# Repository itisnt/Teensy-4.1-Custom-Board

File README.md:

# Teensy-4.1-Custom-Board

Simple Board for a Teensy 4.1 with Ethernet, 2 x I2C, RX1/TX1/GND and the power pins on sockets or pins. I created the board to use it as a sensor board with a Sensirion SHT35D Temp/Humy sensor and a Adafruit four 7-segmented LED Display board.  But maybe somebody can use it for different purposes. 

You need (beside the PCB...):
- A Teensy 4.1 board https://www.pjrc.com/store/teensy41.html
- The Ethernet kit https://www.pjrc.com/store/ethernet_kit.html (you need the MagJack, the capacitor and maybe the headers)
- Additional sockets and headers to make the Teensy removable. 
- If you use I2C, you should add the two SMD 0603 resistors (1 - 10kohm). There are internal pull-ups in the Teensy, but they are quite weak

## Some remarks:
- It's my first KiCad board, so a lot of things will be wrong (i assume...)
- Since i use https://aisler.com to produce the PCB and Aisler allows to simply upload the _pcb file from KiCad, all the Gerber stuff is untested. So don't simply upload the gerber files. Setup KiCad 8 and create your own gerber files
- KiCad 8.0.4 was used
- Since i didn't find the right MagJack in KiCad i had to edit the Symbol for one of the MagJack available in KiCad. What i did was reordering R1-R8. Thats why there is a custom lib. And also you need the Teensy Lib which i've found somewhere in the internet. 
- I do not sell any PCB's

## Ideas for the future:
- Make more pins available (SPI foremost)
- Center the top I2C header so that the Adafruit 4-Segment Display is more in the middle of the board
- Maybe add an FRAM (SPI based)

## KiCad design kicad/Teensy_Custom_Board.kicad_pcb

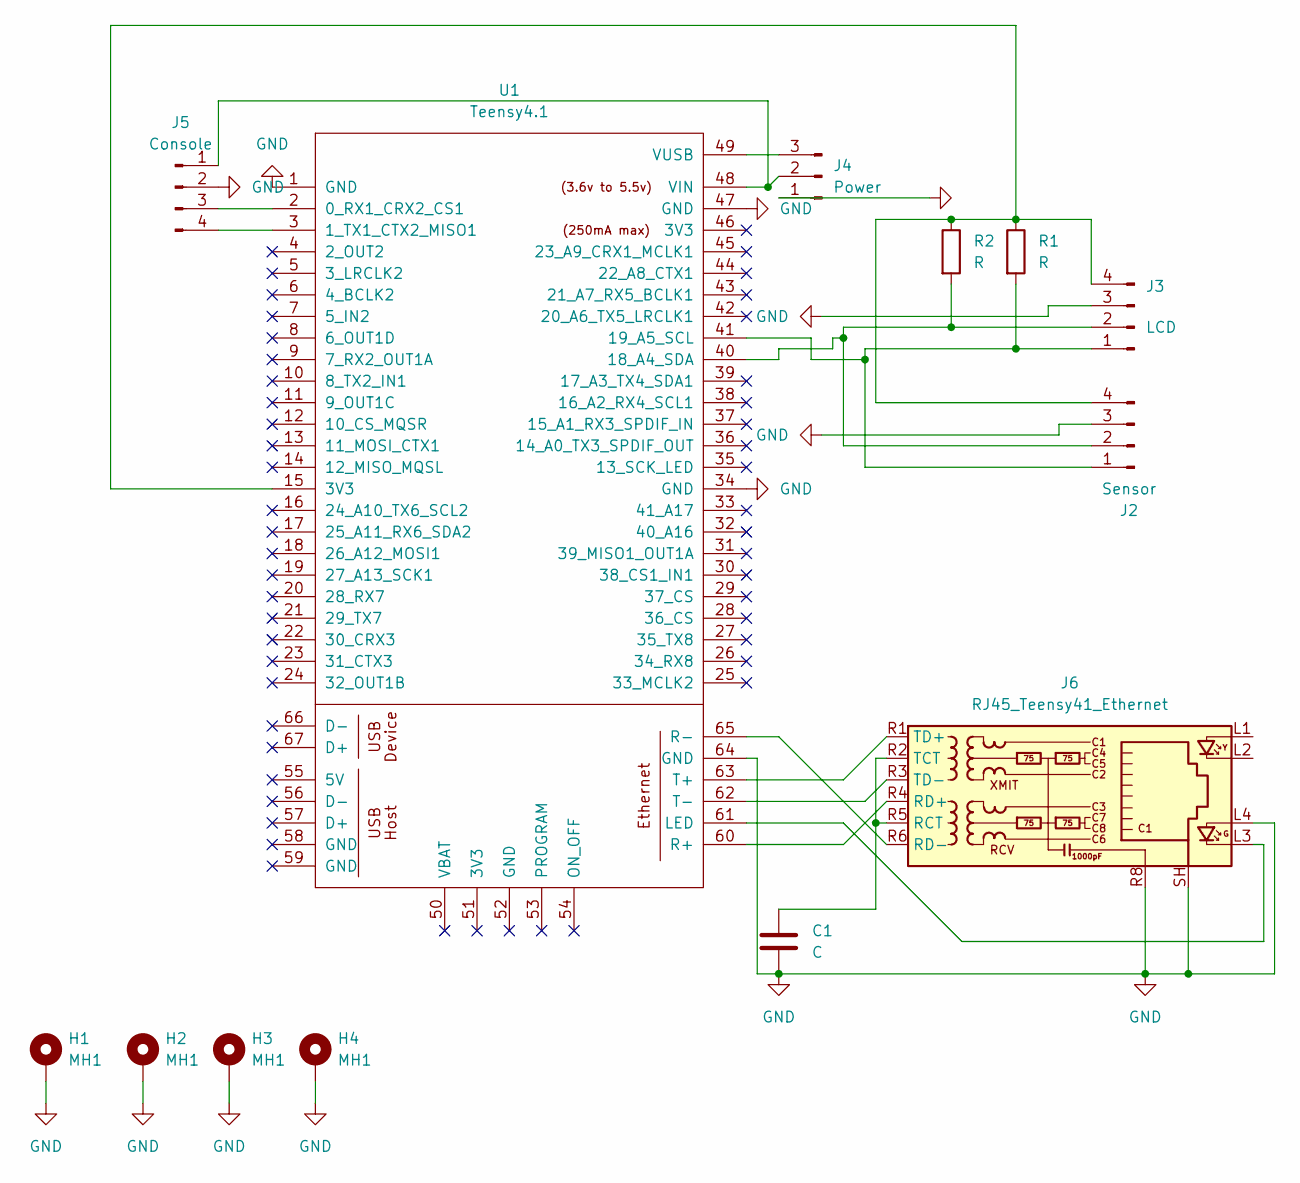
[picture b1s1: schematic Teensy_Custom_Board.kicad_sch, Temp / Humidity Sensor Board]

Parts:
C1: C; C_Disc_D3.0mm_W1.6mm_P2.50mm
H1, H2, H3, H4: MH1; MountingHole_3.5mm_Pad_Via
J2: Sensor; PinHeader_1x04_P2.54mm_Vertical
J3: LCD; PinHeader_1x04_P2.54mm_Vertical
J4: Power; PinHeader_1x03_P2.54mm_Vertical
J5: Console; PinHeader_1x04_P2.54mm_Vertical
J6: RJ45_Teensy41_Ethernet; RJ45_Amphenol_RJMG1BD3B8K1ANR
R1, R2: R; R_0603_1608Metric_Pad0.98x0.95mm_HandSolder
U1: Teensy4.1; Teensy41

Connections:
GND: C1.2, H1.1, H2.1, H3.1, H4.1, J2.3, J3.3, J4.1, J5.2, J6.L4, J6.R8, J6.SH, U1.1 (GND), U1.34 (GND), U1.47 (GND), U1.64 (GND)
unnamed: J2.1, J3.1, R1.2, U1.41 (19_A5_SCL)
unnamed: J2.2, J3.2, R2.2, U1.40 (18_A4_SDA)
unnamed: J2.4, J3.4, R1.1, R2.1, U1.15 (3V3)
unnamed: J4.2, J5.1, U1.48 (VIN)
unnamed: J4.3, U1.49 (VUSB)
unnamed: J5.3, U1.2 (0_RX1_CRX2_CS1)
unnamed: J5.4, U1.3 (1_TX1_CTX2_MISO1)
unnamed: C1.1, J6.R2 (TCT), J6.R5 (RCT)
unnamed: J6.R4 (RD+), U1.60 (R+)
unnamed: J6.R6 (RD-), U1.65 (R-)
unnamed: J6.R1 (TD+), U1.63 (T+)
unnamed: J6.R3 (TD-), U1.62 (T-)
unnamed: J6.L3, U1.61 (LED)

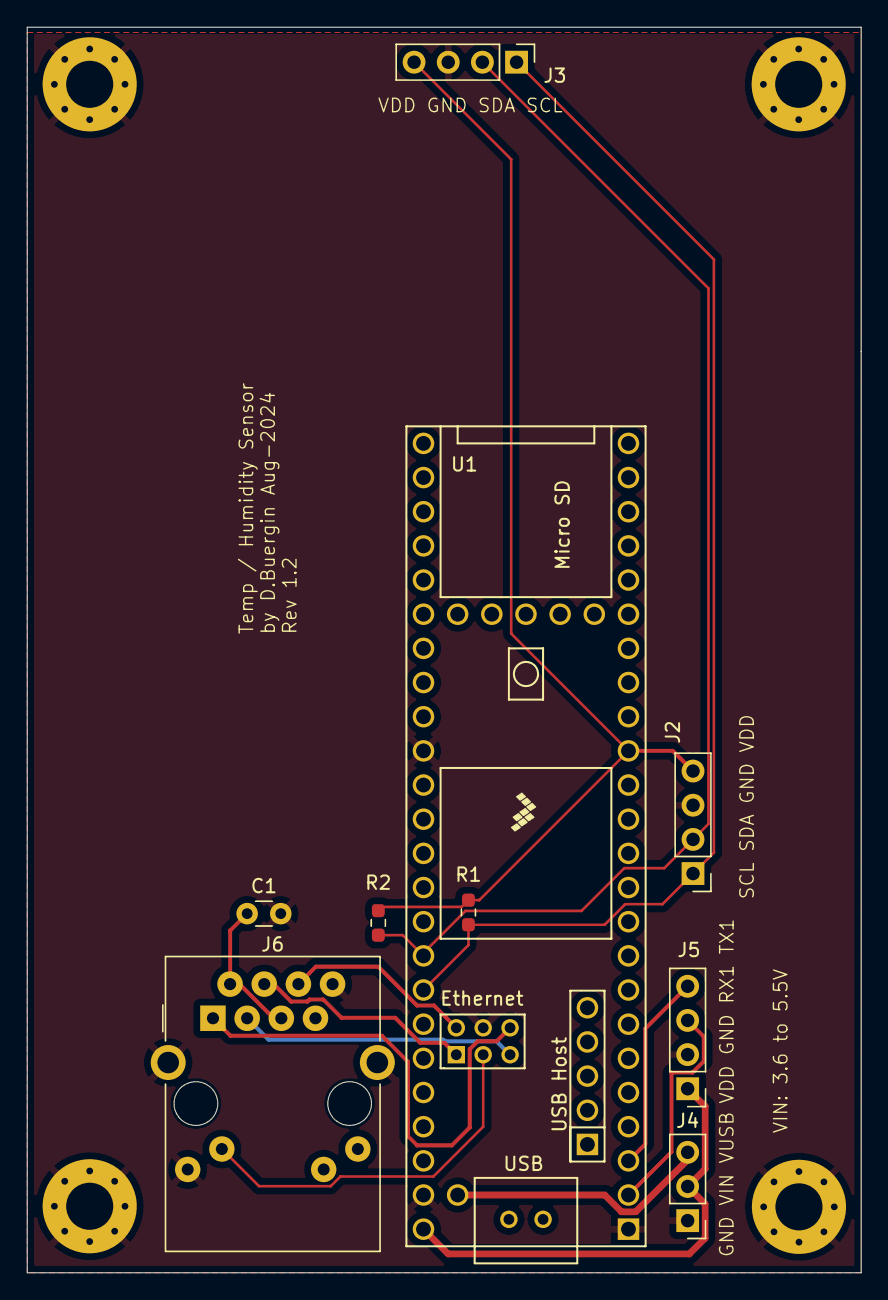
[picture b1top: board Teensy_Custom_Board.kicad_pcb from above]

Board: 2 copper layers, 62.0 x 92.6 mm, 13 parts (0 on the bottom side), 14 nets.

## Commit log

2024-09-09 add text
